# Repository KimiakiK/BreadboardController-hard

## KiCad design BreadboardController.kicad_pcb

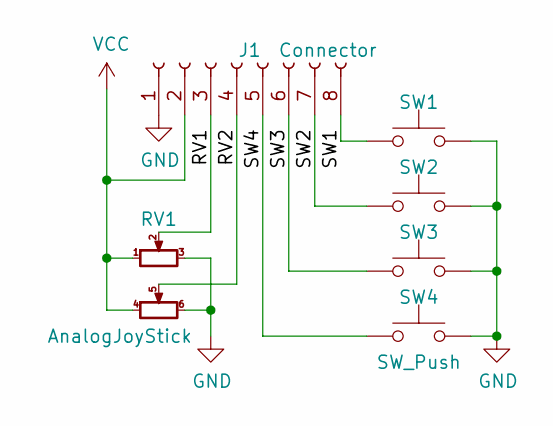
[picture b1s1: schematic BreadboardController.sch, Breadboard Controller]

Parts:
J1: Connector; Connecter_SMD_8pin
RV1: AnalogJoyStick
SW1, SW2, SW3, SW4: SW_Push; SW_SMD

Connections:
/RV1: J1.3, RV1.2
/RV2: J1.4, RV1.5
/SW1: J1.8, SW1.1
/SW2: J1.7, SW2.1
/SW3: J1.6, SW3.1
/SW4: J1.5, SW4.1
GND: J1.1, RV1.3, RV1.6, SW1.2, SW2.2, SW3.2, SW4.2
VCC: J1.2, RV1.1, RV1.4

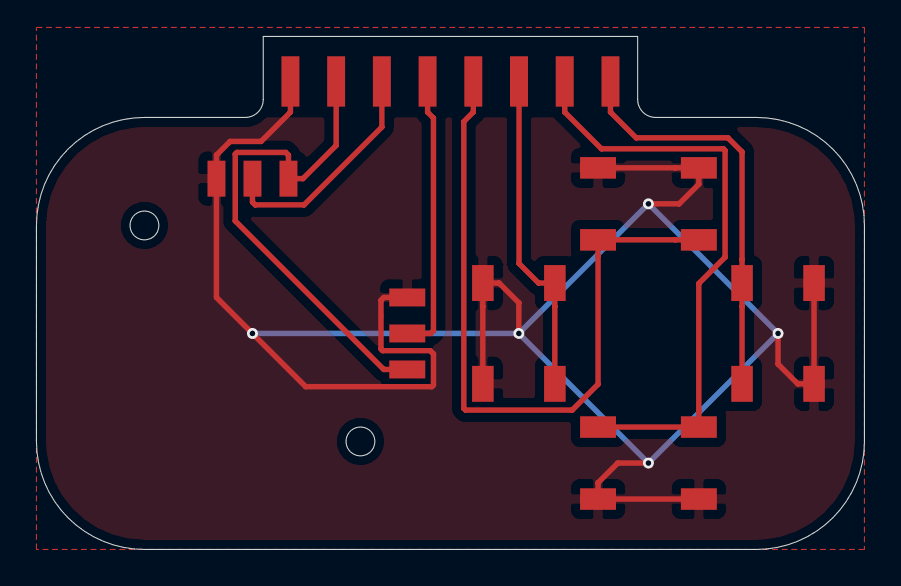
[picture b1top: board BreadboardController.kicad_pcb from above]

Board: 2 copper layers, 46.0 x 28.5 mm, 6 parts (0 on the bottom side), 8 nets.

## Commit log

2021-05-27 基板 V2.0
